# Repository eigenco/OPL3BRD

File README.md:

# OPL3BRD

Simple 8 bit ISA board with OPL3.

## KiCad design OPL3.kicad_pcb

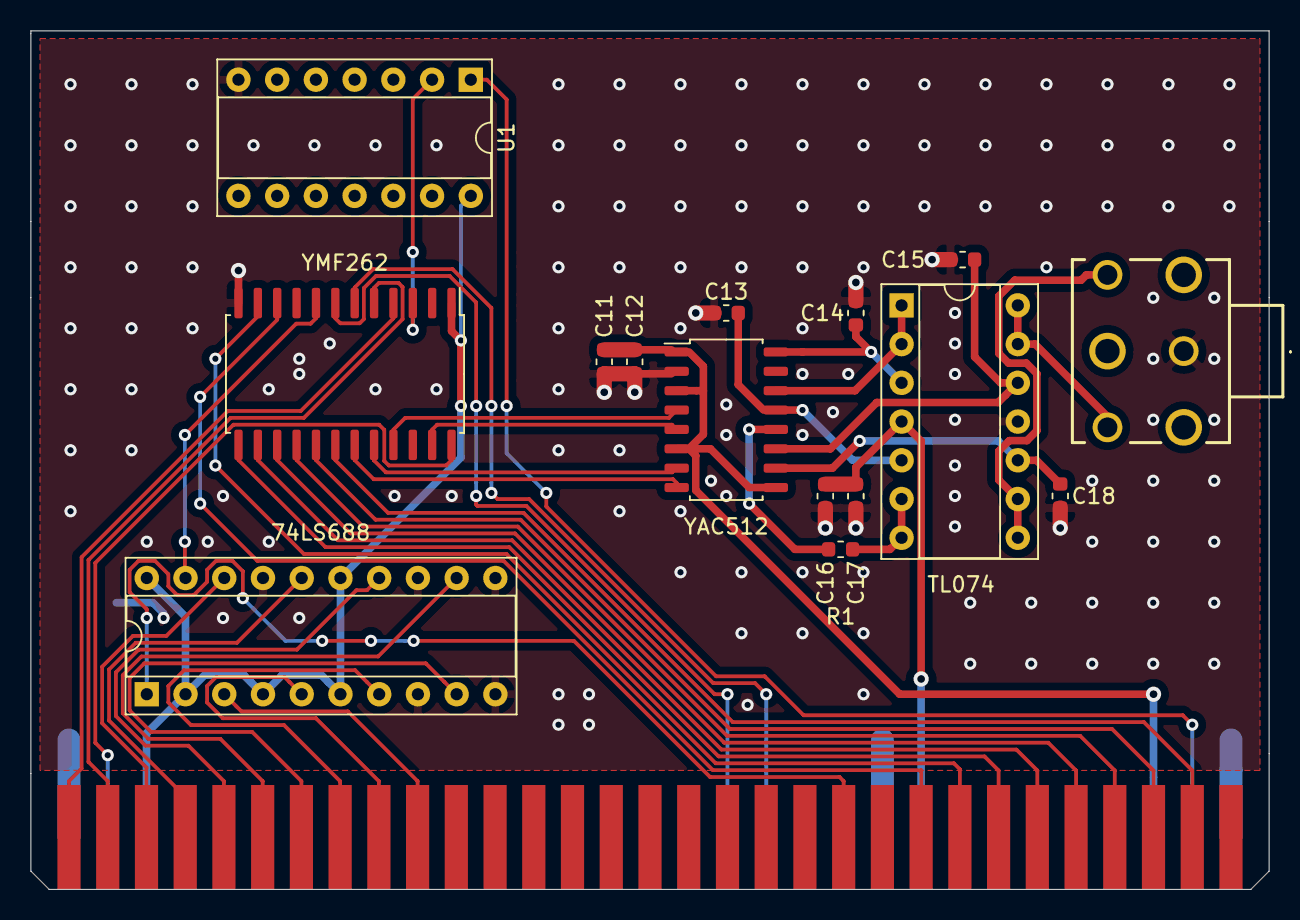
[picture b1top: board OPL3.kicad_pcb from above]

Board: 2 copper layers, 81.2 x 56.3 mm, 16 parts (0 on the bottom side), 41 nets.

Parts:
74LS688: 74LS688; DIP-20_W7.62mm_Socket
C11, C14, C16: 10uF; C_0603_1608Metric
C12, C17: 100nF; C_0603_1608Metric
C13: 68pF; C_0603_1608Metric
C15, C18: 2.7nF; C_0603_1608Metric
J3: Conn_02x03_Counter_Clockwise; STX31003N
J4: Bus_ISA_8bit; BUS_PC
R1: 33; R_0603_1608Metric
TL074: Conn_02x07_Counter_Clockwise; DIP-14_W7.62mm_Socket
U1: 74LS04; DIP-14_W7.62mm_Socket
YAC512: Conn_02x08_Counter_Clockwise; SOP-16_4.55x10.3mm_P1.27mm
YMF262: Conn_02x12_Counter_Clockwise; SOP-24_7.5x15.4mm_P1.27mm

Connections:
A0: J4.62, YMF262.4
A1: J4.61, YMF262.5
A2: 74LS688.18, J4.60
A3: 74LS688.16, J4.59
A4: 74LS688.14, J4.58
A5: 74LS688.12, J4.57
A6: 74LS688.9, J4.56
A7: 74LS688.7, J4.55
A8: 74LS688.5, J4.54
A9: 74LS688.3, J4.53
AEN: 74LS688.1, J4.42
AOUT: C13.1, TL074.5, YAC512.13
CH1: C18.1, TL074.10, YAC512.10
CH2: C15.1, TL074.12, YAC512.11
CV: C14.1, TL074.3, YAC512.16
D0: J4.40, YMF262.10
D1: J4.39, YMF262.11
D2: J4.38, YMF262.13
D3: J4.37, YMF262.14
D4: J4.36, YMF262.15
D5: J4.35, YMF262.16
D6: J4.34, YMF262.17
D7: J4.33, YMF262.18
DACCLK: YAC512.5, YMF262.23
DOAB: YAC512.4, YMF262.21
GND: 74LS688.8, 74LS688.10, 74LS688.11, 74LS688.13, 74LS688.17, C11.1, C12.1, C13.2, C14.2, C15.2, C16.1, C17.1, C18.2, J3.1, J4.1, J4.10, J4.31, TL074.11, U1.7, YAC512.2, YMF262.12
MP: TL074.1, TL074.2, YAC512.14
NRESET: U1.2, YMF262.3
OSC: J4.30, YMF262.24
OUT2: R1.2, TL074.6, TL074.7
OUT3: J3.2, TL074.8, TL074.9
OUT4: J3.5, TL074.13, TL074.14
RESET: J4.2, U1.1
SMPAC: YAC512.7, YMF262.20
SMPBD: YAC512.8, YMF262.19
SWIN: R1.1, YAC512.12
VCC: 74LS688.2, 74LS688.4, 74LS688.6, 74LS688.15, 74LS688.20, C11.2, C12.2, J4.3, J4.29, U1.14, YAC512.1, YAC512.3, YAC512.6, YAC512.9, YMF262.1
VP: C16.2, C17.2, J4.9, TL074.4
~CS: 74LS688.19, YMF262.8
~IOR: J4.14, YMF262.7
~IOW: J4.13, YMF262.6

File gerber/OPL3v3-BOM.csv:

Comment,Designator,Footprint,LCSC Part Number
10uF,"C11, C14, C16",C_0603_1608Metric,C96446
100nF,"C12, C17",C_0603_1608Metric,C57112
2.7nF,"C15, C18",C_0603_1608Metric,C1609
68pF,C13,C_0603_1608Metric,C28262
33,R1,C_0603_1608Metric,C23140
